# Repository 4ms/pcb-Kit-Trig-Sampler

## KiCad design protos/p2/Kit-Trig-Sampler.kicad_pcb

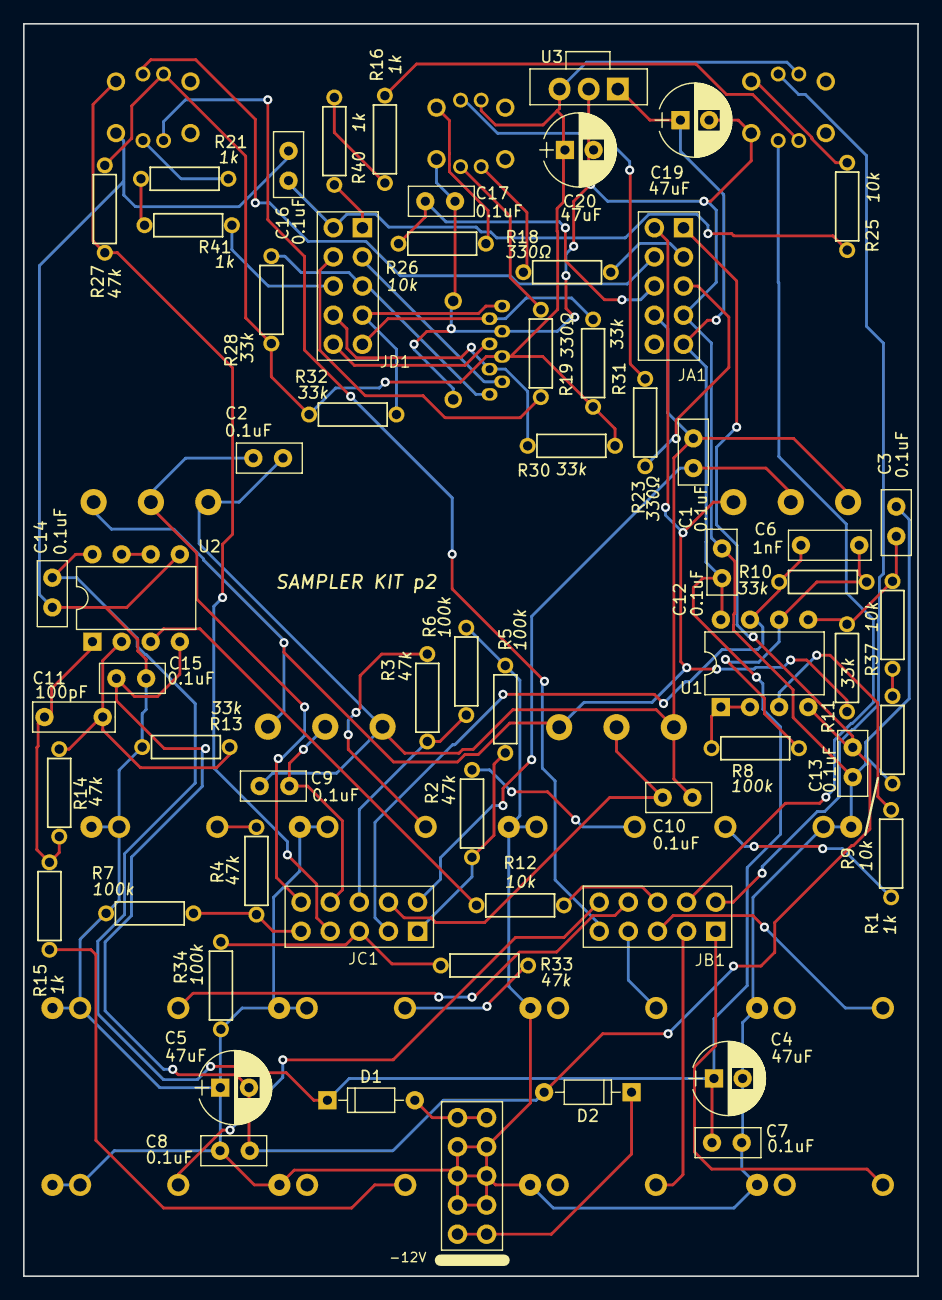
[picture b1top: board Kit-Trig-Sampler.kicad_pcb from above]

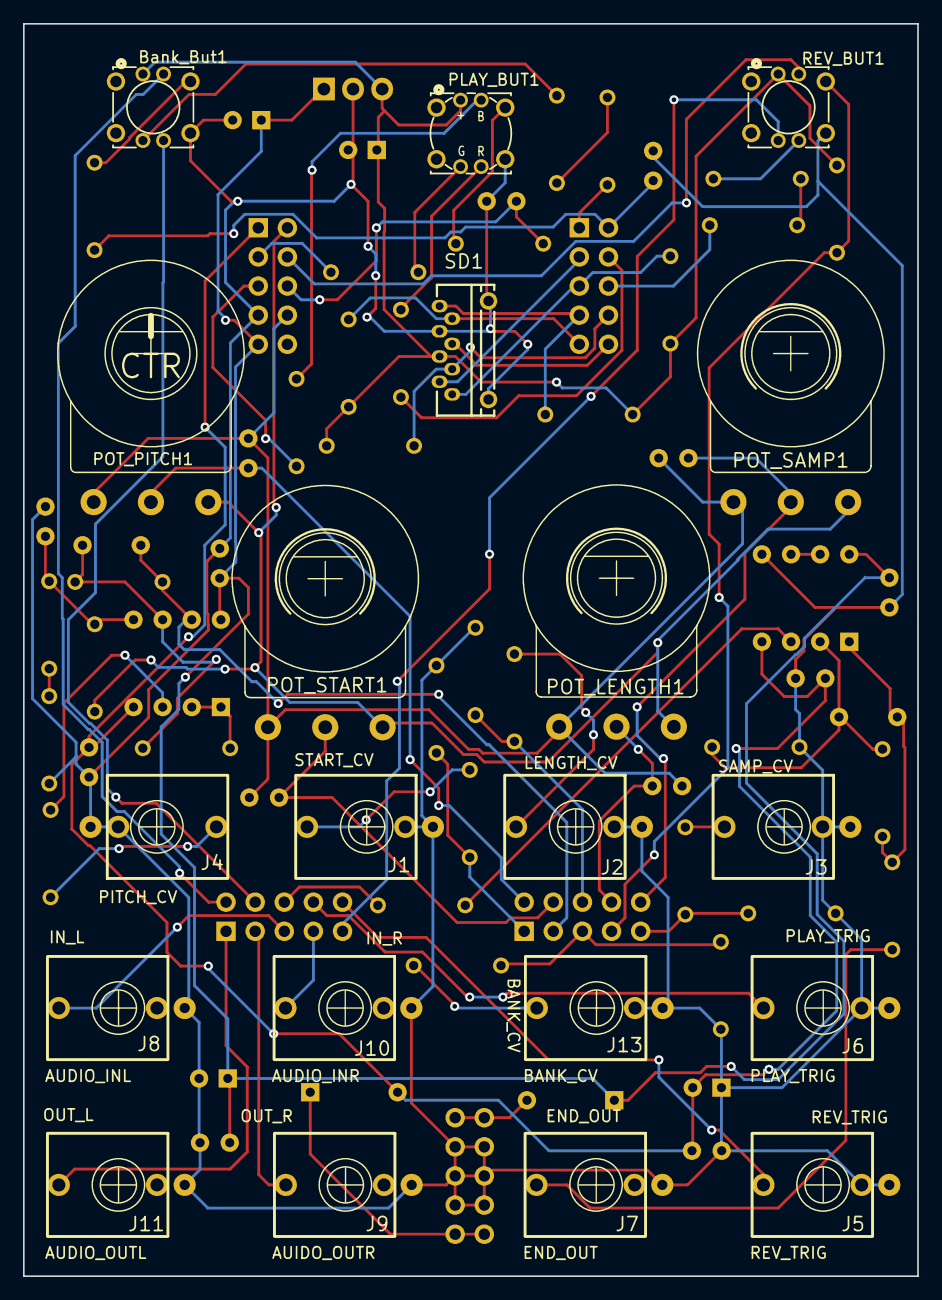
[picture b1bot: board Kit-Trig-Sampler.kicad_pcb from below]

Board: 2 copper layers, 78.0 x 109.2 mm, 81 parts (20 on the bottom side), 66 nets.

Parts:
Bank_But1: Button_SPST_RGB_5.4mmCap; Button_RgbLED_SPST_TC002
C1, C2, C3, C7, C8, C9, C10, C12, C13, C14, C15, C16, C17: 0.1uF_Disc_TH; C_Disc_P2.54mm
C4, C5, C19, C20: 47uF_16V_TH; CP_Radial_P2.5mm
C6: 1nF_Disc_TH; C_Disc_P5.08mm
C11: 100pF_Disc_TH; C_Disc_P5.08mm
D1, D2: SB140-E3_TH; D_DO-35_P7.62mm_Horizontal
J1: START_CV; EighthInch_PJ398SM
J2: LENGTH_CV; EighthInch_PJ398SM
J3: SAMP_CV; EighthInch_PJ398SM
J4: PITCH CV; EighthInch_PJ398SM
J5: REV_TRIG; EighthInch_PJ398SM
J6: PLAY_TRIG; EighthInch_PJ398SM
J7: END_OUT; EighthInch_PJ398SM
J8: AUDIO_INL; EighthInch_PJ398SM
J9: AUIDO_OUTR; EighthInch_PJ398SM
J10: AUDIO_INR; EighthInch_PJ398SM
J11: AUDIO_OUTL; EighthInch_PJ398SM
J13: BANK_CV; EighthInch_PJ398SM
J14: Eurorack_Power_10pin_Unshrouded; Pins_2x05_2.54mm_TH_Europower
JA1: Socket_02x05_TH; Socket_2x05_2.54mm_TH
JB1: Socket_02x05_TH; Socket_2x05_2.54mm_TH
JC1: Socket_02x05_TH; Socket_2x05_2.54mm_TH
JD1: Socket_02x05_TH; Socket_2x05_2.54mm_TH
PLAY_BUT1: Button_SPST_RGB_7mmCap; Button_RgbLED_SPST_PB615303HL-7mm
POT_LENGTH1: 16mm_NoDet_10k; Pot_16mm_NoDet_RV16AF-4A
POT_PITCH1: 16mm_CtrDet_10k; Pot_16mm_CtrDet_RV16AF-4A
POT_SAMP1: 16mm_NoDet_10k; Pot_16mm_NoDet_RV16AF-4A
POT_START1: 16mm_NoDet_10k; Pot_16mm_NoDet_RV16AF-4A
R1, R11, R15, R16, R21, R40, R41: 1k_TH0.125; R_Axial_DIN0207_L6.3mm_D2.5mm_P7.62mm_Horizontal
R2, R3, R4, R14, R33: 47k_TH0.125; R_Axial_DIN0207_L6.3mm_D2.5mm_P7.62mm_Horizontal
R5, R6, R7, R8, R34: 100k_TH0.125; R_Axial_DIN0207_L6.3mm_D2.5mm_P7.62mm_Horizontal
R9, R12, R25, R26, R27, R37: 10k_TH0.125; R_Axial_DIN0207_L6.3mm_D2.5mm_P7.62mm_Horizontal
R10, R13, R28, R30, R31, R32: 33k_TH0.125; R_Axial_DIN0207_L6.3mm_D2.5mm_P7.62mm_Horizontal
R18, R19, R23: 330Ω_TH0.125; R_Axial_DIN0207_L6.3mm_D2.5mm_P7.62mm_Horizontal
REV_BUT1: Button_SPST_RGB_5.4mmCap; Button_RgbLED_SPST_TC002
SD1: microSDCon_Vert_TH_PJS008U-3000; CardSlot_MicroSD_YamaichiPJS008U-3000
U1, U2: TL082_TH; DIP-8pin_TH
U3: 78M33_TH; TO-220-3_PXO78xx-500

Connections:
+3V3: Bank_But1.5 (CA), C20.1, PLAY_BUT1.5 (CA), R27.1, R28.1, R30.1, R31.1, R32.1, REV_BUT1.5 (CA), SD1.4 (VDD), U3.3 (OUT)
+12V: C4.1, C7.1, C12.1, C14.1, C19.1, D1.1 (K), JA1.9 (-12V), U1.8 (V+), U2.8 (V+), U3.1 (IN)
-12VA: C5.2, C8.1, C13.1, C15.1, D2.2 (A), JA1.1 (+12V), U1.4 (V-), U2.4 (V-)
/A0: JC1.1 (+12V), R2.2, R5.2
/A1: C1.1, JC1.2 (+12V), POT_PITCH1.2 (Center)
/A2: C6.1, JC1.3 (GND), R10.1, U1.7
/A3: C10.1, JC1.4 (GND), POT_START1.2 (Center)
/A4: JC1.5 (GND), R33.2, R34.2
/A5: JC1.6 (GND), R3.2, R6.2
/A6: JC1.7 (GND), R27.2, REV_BUT1.2 (POLE-A)
/A7: C9.1, JC1.8 (GND), POT_LENGTH1.2 (Center)
/A8: JC1.9 (-12V), R4.2, R7.2
/A9: C2.1, JC1.10 (-12V), POT_SAMP1.2 (Center)
/AUDIO_IN1: J10.1 (SIG), JB1.7 (GND)
/AUDIO_IN2: J8.1 (SIG), JB1.5 (GND)
/AUDIO_OUT1: J9.1 (SIG), JB1.3 (GND)
/AUDIO_OUT2: J11.1 (SIG), JB1.1 (+12V)
/D0: Bank_But1.6 (G), JB1.2 (+12V)
/D1: Bank_But1.7 (R), JB1.4 (GND)
/D2: J5.1 (SIG), JB1.10 (-12V)
/D3: JB1.9 (-12V), REV_BUT1.8 (B)
/D4: JD1.8 (GND), R30.2, SD1.3 (CMD)
/D5: JD1.1 (+12V), R40.1
/D6: C16.1, JD1.2 (+12V), R25.2
/D7: JD1.6 (GND), R41.1
/D8: JD1.4 (GND), R19.1
/D9: JD1.10 (-12V), SD1.5 (CLK)
/D10: JA1.4 (GND), REV_BUT1.6 (G)
/D11: JA1.3 (GND), R18.1
/D12: C17.1, JA1.6 (GND), R26.2
/D13: J6.1 (SIG), JB1.8 (GND)
/D14: JA1.5 (GND), R23.2
/D15: JB1.6 (GND), R12.1
/D16: JD1.9 (-12V), R31.2, SD1.7 (DAT0)
/D17: JD1.7 (GND), R32.2, SD1.8 (DAT1)
/D18: JD1.5 (GND), R28.2, SD1.1 (DAT2)
/D19: JD1.3 (GND), SD1.2 (CD/DAT3)
GND: Bank_But1.4 (UP-B), C3.1, C4.2, C5.1, C7.2, C8.2, C12.2, C13.2, C14.2, C15.2, C16.2, C17.2, C19.2, C20.2, J1.2 (SHEILD), J1.3 (SW), J2.2 (SHEILD), J2.3 (SW), J3.2 (SHEILD), J3.3 (SW), J4.2 (SHEILD), J4.3 (SW), J5.2 (SHEILD), J5.3 (SW), J6.2 (SHEILD), J6.3 (SW), J7.2 (SHEILD), J8.2 (SHEILD), J9.2 (SHEILD), J10.2 (SHEILD), J11.2 (SHEILD), J13.2 (SHEILD), J13.3 (SW), J14.3 (GND), J14.4 (GND), J14.5 (GND), J14.6 (GND), J14.7 (GND), J14.8 (GND), JA1.7 (GND), PLAY_BUT1.4 (UP-B), R5.1, R6.1, R7.1, R9.1, R13.1, R34.1, REV_BUT1.4 (UP-B), SD1.6 (VSS), SD1.9 (SHELL1), SD1.10 (SHELL2), U2.5 (+), U3.2 (GND)
GNDADC: C1.2, C2.2, C9.2, C10.2, JA1.8 (GND), POT_LENGTH1.1 (Left), POT_PITCH1.1 (Left), POT_SAMP1.1 (Left), POT_START1.1 (Left)
unnamed: Bank_But1.8 (B), R16.2
unnamed: Bank_But1.2 (POLE-A), R25.1
unnamed: C11.2, R14.2, R15.1, U2.1
unnamed: D1.2 (A), J14.1 (+12V), J14.2 (+12V)
unnamed: D2.1 (K), J14.9 (-12V), J14.10 (-12V)
unnamed: J1.1 (SIG), R2.1
unnamed: J2.1 (SIG), R3.1
unnamed: J3.1 (SIG), R4.1
unnamed: J4.1 (SIG), R1.1
unnamed: J7.1 (SIG), R15.2
unnamed: J13.1 (SIG), R33.1
unnamed: PLAY_BUT1.8 (B), R18.2
unnamed: PLAY_BUT1.6 (G), R23.1
unnamed: PLAY_BUT1.2 (POLE-A), R26.1
unnamed: PLAY_BUT1.7 (R), R19.2
unnamed: R16.1, R40.2
unnamed: R21.1, R41.2
unnamed: R9.2, R37.1
unnamed: R21.2, REV_BUT1.7 (R)
unnamed: R1.2, U1.3 (+)
unnamed: R8.1, U1.1, U1.2 (-)
unnamed: C3.2, R11.1, R37.2, U1.5 (+)
unnamed: C6.2, R8.2, R10.2, U1.6 (-)
unnamed: R12.2, U2.3 (+)
unnamed: C11.1, R13.2, R14.1, U2.2 (-)
unnamed: U2.6 (-), U2.7
VREF+: JA1.2 (+12V), POT_LENGTH1.3 (Right), POT_PITCH1.3 (Right), POT_SAMP1.3 (Right), POT_START1.3 (Right), R11.2
